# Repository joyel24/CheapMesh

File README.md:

# CheapMesh

CheapMesh is a pcb arround the HT-CT62 chip by Heltec.

The goal is to get a cheap Meshtastic node with this chip, therefore some corners where cut.

Several componemts are implemented double, just pick what works best for you.

## ToDo
- Add CheapMesh variant to Meshtastic firmware

## PCB

### Antenna 
* Option A: use the onboard antennas
* Option B: use an external antenna with the IPEX connector (and cutting of the onboard lora antenna)
* Option C: use an external antenna with an sma connector (and cutting of the onboard lora antenna)
* Option D: solder on a dipol antenna (and cutting of the onboard lora antenna)
  
### Screen
* Completele optional. Make sure to get a screen with the matching pinout. I recommend SSD1306 128x64 I2C

### 3.3V Regulator
* Option A: use an external 3.3V powersource
* Option C: use a AP211K-3.3 and the correspondending capacitors
* Option B: use a L78L33 and the correspondending capacitors
* Option D: use a [L78L33 pin compatible DC/DC Buck converter like this one](https://aliexpress.com/item/1005005626634245.html?spm=a2g0o.productlist.main.1.1897OyxROyxRry&algo_pvid=5153460b-3c1f-4c8b-b6be-ddba46f5bff5&algo_exp_id=5153460b-3c1f-4c8b-b6be-ddba46f5bff5-0&pdp_npi=4%40dis%21EUR%211.55%210.95%21%21%211.62%210.99%21%402103853617143919371401715e9ea6%2112000033795813043%21sea%21DE%210%21AB&curPageLogUid=g6keG6AFecrJ&utparam-url=scene%3Asearch%7Cquery_from%3A)
  
### Resetting for flashing
* Option A: populate the UMH3N
* Option B: use an external usb serial interface which can reset the chip
* Option C: Connect GND and HT_EN with a wire. Power on the board (by plugging in) and remove the wire.

### Powering the Board
Never connect more than one powersource at a time!!!
* via the usb a pcb connector
* via the usb c connector 
* via the Vin Pins
* via the 3.3V Pins

### Resistors
All Resitors are 1206 SMD Resistors

R1, R2: Pullup Resistors, 10kOhm

R3, R4: USB Inline Resistors, zero-Ohm

R5, R6: USB-C Resistors, 5,1kOhm

If you want to flash and reflash the HT-CT62 on the pcb, you need to populate R1 and R2.
If you not wanna flash the HT-CT62 on the pcb (you have a already programmed chip), you can make a solder bridge on R1.

## Building instructions
1. Source the the pcb yourself.
2. Solder on the components.
3. Flash the ESP.
    * Option A - use an external usb serial interface like CH34X, CP21XX, FTDI or any other serial interface. 
    * Option B - use the usb A pcb port
    * Option C - use the usb c port (Need to solder it)

## BOM
|Reference|Value           |Footprint                                                  |Qty|
|---------|----------------|-----------------------------------------------------------|---|
|AE1,AE2  |Antenna         |                                                           |2  |
|C1,C5    |C_Polarized     |Depending on power source, +uF if it's instable, optionnal |2  |
|C3,C6    |C               |0805 or 2012 metric, value depens on your LDO choice        |2  |
|H2,H3    |MountingHole_Pad|3.2mm M3 DIN965                                            |2  |
|J1       |Conn_01x02_Pin  |Standard 2.54mm headers                                    |2  |
|J2       |Conn_01x09_Pin  |Standard 2.54mm headers                                    |9  |
|J4       |USB_C           |TYPE-C-31-M-12                                             |1  |
|J5       |Conn_Coaxial    |SMA 73251-2120                                             |1  |
|Q1       |UMH3N           |SOT-363                                                    |1  |
|R1,R2    |10kΩ            |1206 or 3216 metric                                        |2  |
|R3,R4    |0Ω SHUNT        |1206 or 3216 metric                                        |2  |
|R5,R6    |5.1kΩ           |1206 or 3216 metric                                        |2  |
|Screen1  |Conn_01x04_Pin  |Standard 2.54mm headers                                    |4  |
|IO02     |Conn_01x01_Pin  |Standard 2.54mm headers                                    |1  |
|U1       |L78L33          |TO-220-3                                                   |1  |
|U2       |HT-CT62         |MCU + RF Module: Heltec HT-CT62                            |1  |
|U3       |AP2112K-3.3     |SOT-23-5                                                   |1  |

 ## License
 <p xmlns:cc="http://creativecommons.org/ns#" xmlns:dct="http://purl.org/dc/terms/"><span property="dct:title">CheapMesh</span> by <span property="cc:attributionName">PaulHausK</span> is licensed under <a href="https://creativecommons.org/licenses/by-sa/4.0/?ref=chooser-v1" target="_blank" rel="license noopener noreferrer" style="display:inline-block;">Creative Commons Attribution-ShareAlike 4.0 International</a></p>

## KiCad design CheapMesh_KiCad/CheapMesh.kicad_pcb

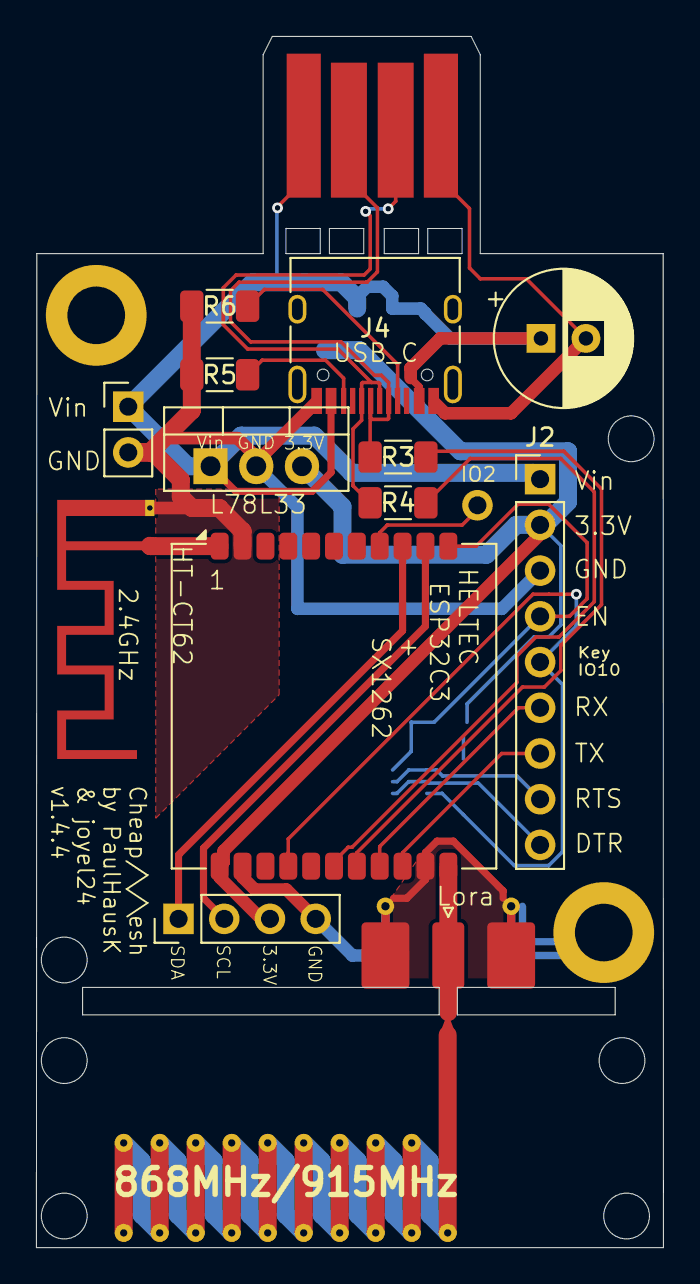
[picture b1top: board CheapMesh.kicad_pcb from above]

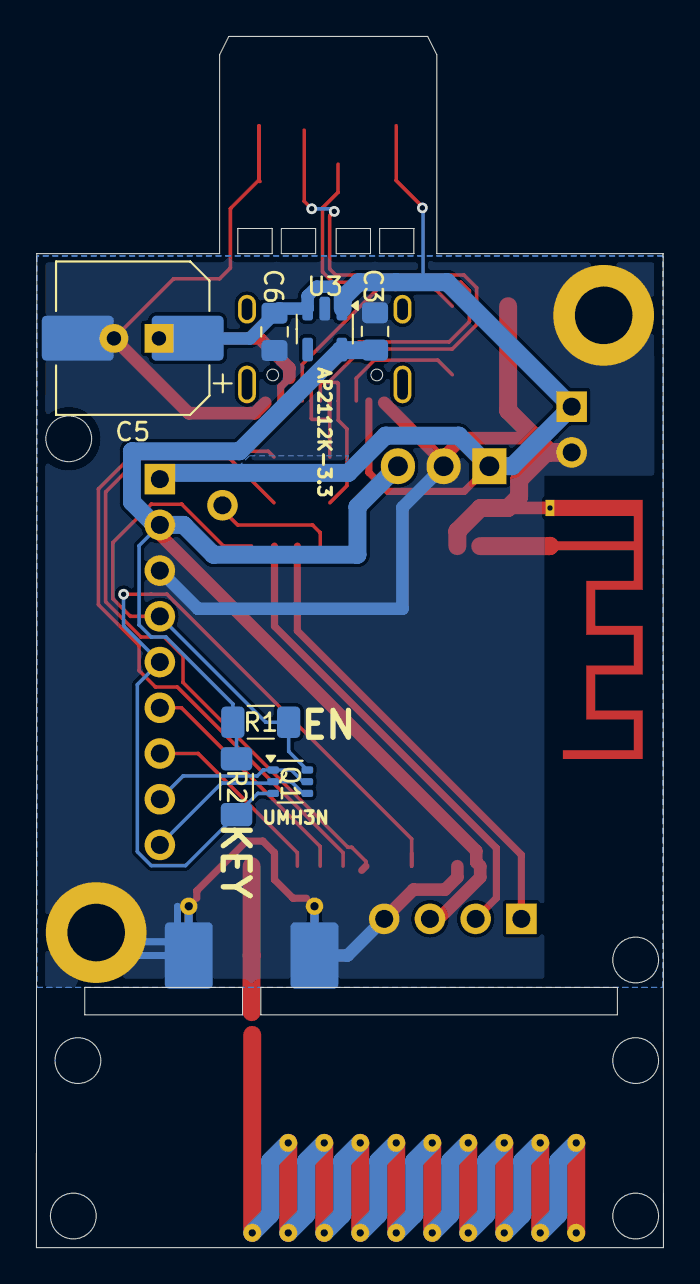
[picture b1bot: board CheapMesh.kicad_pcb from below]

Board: 2 copper layers, 34.8 x 67.3 mm, 24 parts (7 on the bottom side), 19 nets.

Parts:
AE1: Antenna; Texas_SWRA117D_2.4GHz_Left
AE2: Antenna; Texas_SWRA416_868MHz_915MHz
C1: C_Polarized; CP_Radial_D7.5mm_P2.50mm
C3, C6: C; C_0805_2012Metric_Pad1.18x1.45mm_HandSolder
C5: C_Polarized; CP_Elec_8x6.2
H2, H3: MountingHole_Pad; MountingHole_3.2mm_M3_DIN965_Pad
J1: Conn_01x02_Pin; PinHeader_1x02_P2.54mm_Vertical
J2: Conn_01x09_Pin; PinHeader_1x09_P2.54mm_Vertical
J3: USB_A; usb-PCB
J4: USB_C; USB_C_Receptacle_HRO_TYPE-C-31-M-12
J5: Conn_Coaxial; SMA_Molex_73251-2120_EdgeMount_Horizontal
Q1: UMH3N; SOT-363_SC-70-6
R1, R2: 10kΩ; R_1206_3216Metric_Pad1.30x1.75mm_HandSolder
R3, R4: 22Ω; R_1206_3216Metric_Pad1.30x1.75mm_HandSolder
R5, R6: 5.1kΩ; R_1206_3216Metric_Pad1.30x1.75mm_HandSolder
Screen1: Conn_01x04_Pin; PinHeader_1x04_P2.54mm_Vertical
U1: L78L33; TO-220-3_Vertical
U2: HT-CT62; Heltec_HT-CT62
U3: AP2112K-3.3; SOT-23-5

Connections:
3.3V: C3.1, J2.2, R1.1, R2.1, Screen1.3, U1.3 (OUT), U2.12 (VDD), U3.5 (VOUT)
DTR: J2.9, Q1.2 (B1), Q1.4 (E2)
GND: C1.2, C3.2, C5.2, C6.2, H2.1, H3.1, J1.2, J2.3, J3.4 (GND), J4.A1 (GND), J4.A12 (GND), J4.B1 (GND), J4.B12 (GND), J5.2 (Ext), R5.2, R6.2, Screen1.4, U1.2 (GND), U2.2 (GND), U2.13 (GND), U2.21 (GND), U3.2 (GND)
HT_EN: J2.4, Q1.6 (C1), R1.2, U2.11 (EN)
HT_RX: J2.6, U2.19 (GPIO20_RXD)
HT_TX: J2.7, U2.20 (GPIO21_TXD)
unnamed: AE1.1 (A), U2.1 (2.4G_Ant)
unnamed: AE2.1 (A), J5.1 (In), U2.22 (LoRa_Ant)
unnamed: J3.3 (D+), J4.A6 (D+), J4.B6 (D+), R4.1
unnamed: J3.2 (D-), J4.A7 (D-), J4.B7 (D-), R3.1
unnamed: J4.A5 (CC1), R6.1
unnamed: J4.B5 (CC2), R5.1
RTS: J2.8, Q1.1 (E1), Q1.5 (B2)
SCL: Screen1.2, U2.10 (GPIO0)
SDA: Screen1.1, U2.9 (GPIO1)
USB_D+: R4.2, U2.17 (GPIO18_DN)
USB_D-: R3.2, U2.18 (GPIO19_DP)
User_Key: J2.5, Q1.3 (C2), R2.2, U2.15 (GPIO9)
Vin: C1.1, C5.1, C6.1, J1.1, J2.1, J3.1 (VBUS), J4.A4 (VBUS), J4.A9 (VBUS), J4.B4 (VBUS), J4.B9 (VBUS), U1.1 (IN), U3.1 (VIN), U3.3 (EN)

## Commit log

2024-05-01 v1.4.2
2024-07-03 add .gitignore
2024-07-03 ignore .lck files
2024-07-03 ignore CheapMesh-backups
2024-07-03 kicad autoUpdate, no changes
2024-07-03 invert USB_D+ USB_D- in schematics
2024-07-03 remove fp-info-cache
2024-07-03 invert USB_D+ USB_D- in pcb
2024-07-03 update PNGs
2024-10-20 add gpio2 pin
2024-10-20 update pcb PNG
2024-12-07 fix HT-CT62 footprint
2024-12-07 fix D+/- circuit
2024-12-07 GPIO num visible on PC
2024-12-07 update version
